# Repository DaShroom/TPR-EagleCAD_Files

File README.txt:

Ok, Tis licensed under CC-By Sa, which is at the bottom

This is all the electronics stuff for the robot, nuff said

You can also use this under the terms of the CERN license

CREATIVE COMMONS CORPORATION IS NOT A LAW FIRM AND DOES NOT PROVIDE LEGAL SERVICES. DISTRIBUTION OF THIS LICENSE DOES NOT CREATE AN ATTORNEY-CLIENT RELATIONSHIP. CREATIVE COMMONS PROVIDES THIS INFORMATION ON AN "AS-IS" BASIS. CREATIVE COMMONS MAKES NO WARRANTIES REGARDING THE INFORMATION PROVIDED, AND DISCLAIMS LIABILITY FOR DAMAGES RESULTING FROM ITS USE.
License

THE WORK (AS DEFINED BELOW) IS PROVIDED UNDER THE TERMS OF THIS CREATIVE COMMONS PUBLIC LICENSE ("CCPL" OR "LICENSE"). THE WORK IS PROTECTED BY COPYRIGHT AND/OR OTHER APPLICABLE LAW. ANY USE OF THE WORK OTHER THAN AS AUTHORIZED UNDER THIS LICENSE OR COPYRIGHT LAW IS PROHIBITED.

BY EXERCISING ANY RIGHTS TO THE WORK PROVIDED HERE, YOU ACCEPT AND AGREE TO BE BOUND BY THE TERMS OF THIS LICENSE. TO THE EXTENT THIS LICENSE MAY BE CONSIDERED TO BE A CONTRACT, THE LICENSOR GRANTS YOU THE RIGHTS CONTAINED HERE IN CONSIDERATION OF YOUR ACCEPTANCE OF SUCH TERMS AND CONDITIONS.

1. Definitions

"Adaptation" means a work based upon the Work, or upon the Work and other pre-existing works, such as a translation, adaptation, derivative work, arrangement of music or other alterations of a literary or artistic work, or phonogram or performance and includes cinematographic adaptations or any other form in which the Work may be recast, transformed, or adapted including in any form recognizably derived from the original, except that a work that constitutes a Collection will not be considered an Adaptation for the purpose of this License. For the avoidance of doubt, where the Work is a musical work, performance or phonogram, the synchronization of the Work in timed-relation with a moving image ("synching") will be considered an Adaptation for the purpose of this License.
"Collection" means a collection of literary or artistic works, such as encyclopedias and anthologies, or performances, phonograms or broadcasts, or other works or subject matter other than works listed in Section 1(f) below, which, by reason of the selection and arrangement of their contents, constitute intellectual creations, in which the Work is included in its entirety in unmodified form along with one or more other contributions, each constituting separate and independent works in themselves, which together are assembled into a collective whole. A work that constitutes a Collection will not be considered an Adaptation (as defined below) for the purposes of this License.
"Creative Commons Compatible License" means a license that is listed at http://creativecommons.org/compatiblelicenses that has been approved by Creative Commons as being essentially equivalent to this License, including, at a minimum, because that license: (i) contains terms that have the same purpose, meaning and effect as the License Elements of this License; and, (ii) explicitly permits the relicensing of adaptations of works made available under that license under this License or a Creative Commons jurisdiction license with the same License Elements as this License.
"Distribute" means to make available to the public the original and copies of the Work or Adaptation, as appropriate, through sale or other transfer of ownership.
"License Elements" means the following high-level license attributes as selected by Licensor and indicated in the title of this License: Attribution, ShareAlike.
"Licensor" means the individual, individuals, entity or entities that offer(s) the Work under the terms of this License.
"Original Author" means, in the case of a literary or artistic work, the individual, individuals, entity or entities who created the Work or if no individual or entity can be identified, the publisher; and in addition (i) in the case of a performance the actors, singers, musicians, dancers, and other persons who act, sing, deliver, declaim, play in, interpret or otherwise perform literary or artistic works or expressions of folklore; (ii) in the case of a phonogram the producer being the person or legal entity who first fixes the sounds of a performance or other sounds; and, (iii) in the case of broadcasts, the organization that transmits the broadcast.
"Work" means the literary and/or artistic work offered under the terms of this License including without limitation any production in the literary, scientific and artistic domain, whatever may be the mode or form of its expression including digital form, such as a book, pamphlet and other writing; a lecture, address, sermon or other work of the same nature; a dramatic or dramatico-musical work; a choreographic work or entertainment in dumb show; a musical composition with or without words; a cinematographic work to which are assimilated works expressed by a process analogous to cinematography; a work of drawing, painting, architecture, sculpture, engraving or lithography; a photographic work to which are assimilated works expressed by a process analogous to photography; a work of applied art; an illustration, map, plan, sketch or three-dimensional work relative to geography, topography, architecture or science; a performance; a broadcast; a phonogram; a compilation of data to the extent it is protected as a copyrightable work; or a work performed by a variety or circus performer to the extent it is not otherwise considered a literary or artistic work.
"You" means an individual or entity exercising rights under this License who has not previously violated the terms of this License with respect to the Work, or who has received express permission from the Licensor to exercise rights under this License despite a previous violation.
"Publicly Perform" means to perform public recitations of the Work and to communicate to the public those public recitations, by any means or process, including by wire or wireless means or public digital performances; to make available to the public Works in such a way that members of the public may access these Works from a place and at a place individually chosen by them; to perform the Work to the public by any means or process and the communication to the public of the performances of the Work, including by public digital performance; to broadcast and rebroadcast the Work by any means including signs, sounds or images.
"Reproduce" means to make copies of the Work by any means including without limitation by sound or visual recordings and the right of fixation and reproducing fixations of the Work, including storage of a protected performance or phonogram in digital form or other electronic medium.
2. Fair Dealing Rights. Nothing in this License is intended to reduce, limit, or restrict any uses free from copyright or rights arising from limitations or exceptions that are provided for in connection with the copyright protection under copyright law or other applicable laws.

3. License Grant. Subject to the terms and conditions of this License, Licensor hereby grants You a worldwide, royalty-free, non-exclusive, perpetual (for the duration of the applicable copyright) license to exercise the rights in the Work as stated below:

to Reproduce the Work, to incorporate the Work into one or more Collections, and to Reproduce the Work as incorporated in the Collections;
to create and Reproduce Adaptations provided that any such Adaptation, including any translation in any medium, takes reasonable steps to clearly label, demarcate or otherwise identify that changes were made to the original Work. For example, a translation could be marked "The original work was translated from English to Spanish," or a modification could indicate "The original work has been modified.";
to Distribute and Publicly Perform the Work including as incorporated in Collections; and,
to Distribute and Publicly Perform Adaptations.
For the avoidance of doubt:

Non-waivable Compulsory License Schemes. In those jurisdictions in which the right to collect royalties through any statutory or compulsory licensing scheme cannot be waived, the Licensor reserves the exclusive right to collect such royalties for any exercise by You of the rights granted under this License;
Waivable Compulsory License Schemes. In those jurisdictions in which the right to collect royalties through any statutory or compulsory licensing scheme can be waived, the Licensor waives the exclusive right to collect such royalties for any exercise by You of the rights granted under this License; and,
Voluntary License Schemes. The Licensor waives the right to collect royalties, whether individually or, in the event that the Licensor is a member of a collecting society that administers voluntary licensing schemes, via that society, from any exercise by You of the rights granted under this License.
The above rights may be exercised in all media and formats whether now known or hereafter devised. The above rights include the right to make such modifications as are technically necessary to exercise the rights in other media and formats. Subject to Section 8(f), all rights not expressly granted by Licensor are hereby reserved.

4. Restrictions. The license granted in Section 3 above is expressly made subject to and limited by the following restrictions:

You may Distribute or Publicly Perform the Work only under the terms of this License. You must include a copy of, or the Uniform Resource Identifier (URI) for, this License with every copy of the Work You Distribute or Publicly Perform. You may not offer or impose any terms on the Work that restrict the terms of this License or the ability of the recipient of the Work to exercise the rights granted to that recipient under the terms of the License. You may not sublicense the Work. You must keep intact all notices that refer to this License and to the disclaimer of warranties with every copy of the Work You Distribute or Publicly Perform. When You Distribute or Publicly Perform the Work, You may not impose any effective technological measures on the Work that restrict the ability of a recipient of the Work from You to exercise the rights granted to that recipient under the terms of the License. This Section 4(a) applies to the Work as incorporated in a Collection, but this does not require the Collection apart from the Work itself to be made subject to the terms of this License. If You create a Collection, upon notice from any Licensor You must, to the extent practicable, remove from the Collection any credit as required by Section 4(c), as requested. If You create an Adaptation, upon notice from any Licensor You must, to the extent practicable, remove from the Adaptation any credit as required by Section 4(c), as requested.
You may Distribute or Publicly Perform an Adaptation only under the terms of: (i) this License; (ii) a later version of this License with the same License Elements as this License; (iii) a Creative Commons jurisdiction license (either this or a later license version) that contains the same License Elements as this License (e.g., Attribution-ShareAlike 3.0 US)); (iv) a Creative Commons Compatible License. If you license the Adaptation under one of the licenses mentioned in (iv), you must comply with the terms of that license. If you license the Adaptation under the terms of any of the licenses mentioned in (i), (ii) or (iii) (the "Applicable License"), you must comply with the terms of the Applicable License generally and the following provisions: (I) You must include a copy of, or the URI for, the Applicable License with every copy of each Adaptation You Distribute or Publicly Perform; (II) You may not offer or impose any terms on the Adaptation that restrict the terms of the Applicable License or the ability of the recipient of the Adaptation to exercise the rights granted to that recipient under the terms of the Applicable License; (III) You must keep intact all notices that refer to the Applicable License and to the disclaimer of warranties with every copy of the Work as included in the Adaptation You Distribute or Publicly Perform; (IV) when You Distribute or Publicly Perform the Adaptation, You may not impose any effective technological measures on the Adaptation that restrict the ability of a recipient of the Adaptation from You to exercise the rights granted to that recipient under the terms of the Applicable License. This Section 4(b) applies to the Adaptation as incorporated in a Collection, but this does not require the Collection apart from the Adaptation itself to be made subject to the terms of the Applicable License.
If You Distribute, or Publicly Perform the Work or any Adaptations or Collections, You must, unless a request has been made pursuant to Section 4(a), keep intact all copyright notices for the Work and provide, reasonable to the medium or means You are utilizing: (i) the name of the Original Author (or pseudonym, if applicable) if supplied, and/or if the Original Author and/or Licensor designate another party or parties (e.g., a sponsor institute, publishing entity, journal) for attribution ("Attribution Parties") in Licensor's copyright notice, terms of service or by other reasonable means, the name of such party or parties; (ii) the title of the Work if supplied; (iii) to the extent reasonably practicable, the URI, if any, that Licensor specifies to be associated with the Work, unless such URI does not refer to the copyright notice or licensing information for the Work; and (iv) , consistent with Ssection 3(b), in the case of an Adaptation, a credit identifying the use of the Work in the Adaptation (e.g., "French translation of the Work by Original Author," or "Screenplay based on original Work by Original Author"). The credit required by this Section 4(c) may be implemented in any reasonable manner; provided, however, that in the case of a Adaptation or Collection, at a minimum such credit will appear, if a credit for all contributing authors of the Adaptation or Collection appears, then as part of these credits and in a manner at least as prominent as the credits for the other contributing authors. For the avoidance of doubt, You may only use the credit required by this Section for the purpose of attribution in the manner set out above and, by exercising Your rights under this License, You may not implicitly or explicitly assert or imply any connection with, sponsorship or endorsement by the Original Author, Licensor and/or Attribution Parties, as appropriate, of You or Your use of the Work, without the separate, express prior written permission of the Original Author, Licensor and/or Attribution Parties.
Except as otherwise agreed in writing by the Licensor or as may be otherwise permitted by applicable law, if You Reproduce, Distribute or Publicly Perform the Work either by itself or as part of any Adaptations or Collections, You must not distort, mutilate, modify or take other derogatory action in relation to the Work which would be prejudicial to the Original Author's honor or reputation. Licensor agrees that in those jurisdictions (e.g. Japan), in which any exercise of the right granted in Section 3(b) of this License (the right to make Adaptations) would be deemed to be a distortion, mutilation, modification or other derogatory action prejudicial to the Original Author's honor and reputation, the Licensor will waive or not assert, as appropriate, this Section, to the fullest extent permitted by the applicable national law, to enable You to reasonably exercise Your right under Section 3(b) of this License (right to make Adaptations) but not otherwise.
5. Representations, Warranties and Disclaimer

UNLESS OTHERWISE MUTUALLY AGREED TO BY THE PARTIES IN WRITING, LICENSOR OFFERS THE WORK AS-IS AND MAKES NO REPRESENTATIONS OR WARRANTIES OF ANY KIND CONCERNING THE WORK, EXPRESS, IMPLIED, STATUTORY OR OTHERWISE, INCLUDING, WITHOUT LIMITATION, WARRANTIES OF TITLE, MERCHANTIBILITY, FITNESS FOR A PARTICULAR PURPOSE, NONINFRINGEMENT, OR THE ABSENCE OF LATENT OR OTHER DEFECTS, ACCURACY, OR THE PRESENCE OF ABSENCE OF ERRORS, WHETHER OR NOT DISCOVERABLE. SOME JURISDICTIONS DO NOT ALLOW THE EXCLUSION OF IMPLIED WARRANTIES, SO SUCH EXCLUSION MAY NOT APPLY TO YOU.

6. Limitation on Liability. EXCEPT TO THE EXTENT REQUIRED BY APPLICABLE LAW, IN NO EVENT WILL LICENSOR BE LIABLE TO YOU ON ANY LEGAL THEORY FOR ANY SPECIAL, INCIDENTAL, CONSEQUENTIAL, PUNITIVE OR EXEMPLARY DAMAGES ARISING OUT OF THIS LICENSE OR THE USE OF THE WORK, EVEN IF LICENSOR HAS BEEN ADVISED OF THE POSSIBILITY OF SUCH DAMAGES.

7. Termination

This License and the rights granted hereunder will terminate automatically upon any breach by You of the terms of this License. Individuals or entities who have received Adaptations or Collections from You under this License, however, will not have their licenses terminated provided such individuals or entities remain in full compliance with those licenses. Sections 1, 2, 5, 6, 7, and 8 will survive any termination of this License.
Subject to the above terms and conditions, the license granted here is perpetual (for the duration of the applicable copyright in the Work). Notwithstanding the above, Licensor reserves the right to release the Work under different license terms or to stop distributing the Work at any time; provided, however that any such election will not serve to withdraw this License (or any other license that has been, or is required to be, granted under the terms of this License), and this License will continue in full force and effect unless terminated as stated above.
8. Miscellaneous

Each time You Distribute or Publicly Perform the Work or a Collection, the Licensor offers to the recipient a license to the Work on the same terms and conditions as the license granted to You under this License.
Each time You Distribute or Publicly Perform an Adaptation, Licensor offers to the recipient a license to the original Work on the same terms and conditions as the license granted to You under this License.
If any provision of this License is invalid or unenforceable under applicable law, it shall not affect the validity or enforceability of the remainder of the terms of this License, and without further action by the parties to this agreement, such provision shall be reformed to the minimum extent necessary to make such provision valid and enforceable.
No term or provision of this License shall be deemed waived and no breach consented to unless such waiver or consent shall be in writing and signed by the party to be charged with such waiver or consent.
This License constitutes the entire agreement between the parties with respect to the Work licensed here. There are no understandings, agreements or representations with respect to the Work not specified here. Licensor shall not be bound by any additional provisions that may appear in any communication from You. This License may not be modified without the mutual written agreement of the Licensor and You.
The rights granted under, and the subject matter referenced, in this License were drafted utilizing the terminology of the Berne Convention for the Protection of Literary and Artistic Works (as amended on September 28, 1979), the Rome Convention of 1961, the WIPO Copyright Treaty of 1996, the WIPO Performances and Phonograms Treaty of 1996 and the Universal Copyright Convention (as revised on July 24, 1971). These rights and subject matter take effect in the relevant jurisdiction in which the License terms are sought to be enforced according to the corresponding provisions of the implementation of those treaty provisions in the applicable national law. If the standard suite of rights granted under applicable copyright law includes additional rights not granted under this License, such additional rights are deemed to be included in the License; this License is not intended to restrict the license of any rights under applicable law.
Creative Commons Notice

Creative Commons is not a party to this License, and makes no warranty whatsoever in connection with the Work. Creative Commons will not be liable to You or any party on any legal theory for any damages whatsoever, including without limitation any general, special, incidental or consequential damages arising in connection to this license. Notwithstanding the foregoing two (2) sentences, if Creative Commons has expressly identified itself as the Licensor hereunder, it shall have all rights and obligations of Licensor.

Except for the limited purpose of indicating to the public that the Work is licensed under the CCPL, Creative Commons does not authorize the use by either party of the trademark "Creative Commons" or any related trademark or logo of Creative Commons without the prior written consent of Creative Commons. Any permitted use will be in compliance with Creative Commons' then-current trademark usage guidelines, as may be published on its website or otherwise made available upon request from time to time. For the avoidance of doubt, this trademark restriction does not form part of the License.

Creative Commons may be contacted at http://creativecommons.org/.

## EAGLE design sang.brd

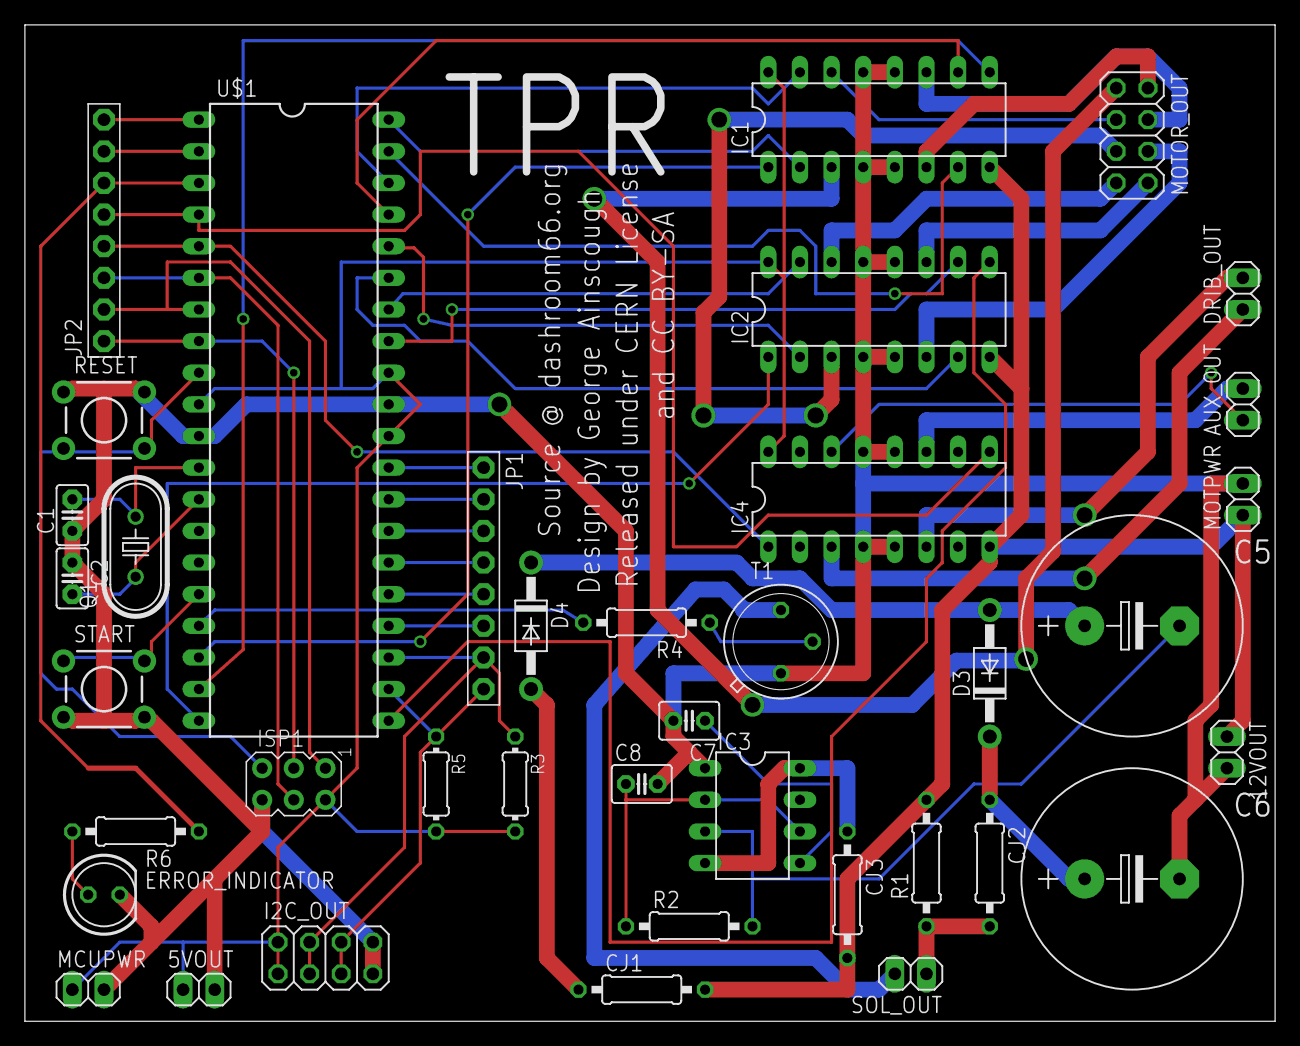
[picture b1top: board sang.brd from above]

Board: 2 copper layers, 100.4 x 80.0 mm, 39 parts (0 on the bottom side), 59 nets.

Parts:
5VOUT, 12VOUT: 1X02
AUX_OUT: 1X02
C1, C2: 22pF; C2.5-2
C5, C6: E7,5-18
C7: 100nF; C025-030X050
C8: 1nF; C025-030X050
CJ1, CJ2, CJ3: 0207/10
D3, D4: 1N4004; DO41-10
DRIB_OUT: 1X02
ERROR_INDICATOR: LED5MM
I2C_OUT: 2X04
IC1, IC2, IC4: L293D; DIL16
IC3: NE555; DIL-08
ISP1: AVRISP-6; AVRISP
JP1, JP2: 1X08-BIG
MCUPWR: 1X02
MOTOR_OUT: 2X04
MOTPWR: 1X02
Q1: 16MHz; HC49U70
R1, R4: 10K; 0207/10
R2: 33K; 0207/10
R3, R5: 0204/7
R6: 220; 0207/10
RESET: TACTILE-PTH
SOL_OUT: 1X02
START: TACTILE-PTH
T1: TO39
U$1: ATMEGA644*; ATMEGA644

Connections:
+5V: 5VOUT.1, I2C_OUT.1, I2C_OUT.2, IC1.16, IC2.16, IC4.16, ISP1.2, MCUPWR.1, R3.2, R5.2, U$1.10, U$1.30, U$1.32
+12V: 12VOUT.1, CJ1.2, CJ3.2, IC1.8, IC2.8, IC4.8, MOTPWR.1, R1.2
+24V: CJ2.2, R1.1, SOL_OUT.1
ERROR_LED: JP2.6, R6.1, U$1.3
GND: 5VOUT.2, 12VOUT.2, C1.1, C2.1, C6.-, C7.2, C8.2, ERROR_INDICATOR.K, I2C_OUT.7, I2C_OUT.8, IC1.4, IC1.5, IC1.12, IC1.13, IC2.4, IC2.5, IC2.12, IC2.13, IC3.1, IC4.4, IC4.5, IC4.12, IC4.13, ISP1.6, MCUPWR.2, MOTPWR.2, RESET.1, RESET.2, START.3, START.4, T1.1, U$1.11, U$1.31
GO: START.1, START.2, U$1.16
M1+: IC1.3, MOTOR_OUT.1
M1-: IC1.6, MOTOR_OUT.2
M1F: IC1.2, U$1.40
M1PWM: IC1.1, U$1.18
M1R: IC1.7, U$1.39
M2+: IC1.14, MOTOR_OUT.3
M2-: IC1.11, MOTOR_OUT.4
M2F: IC1.15, U$1.38
M2PWM: IC1.9, U$1.19
M2R: IC1.10, U$1.37
M3+: IC2.3, MOTOR_OUT.5
M3-: IC2.6, MOTOR_OUT.6
M3F: IC2.2, U$1.36
M3PWM: IC2.1, U$1.20
M3R: IC2.7, U$1.35
M4+: IC2.14, MOTOR_OUT.7
M4-: IC2.11, MOTOR_OUT.8
M4F: IC2.15, U$1.34
M4PWM: IC2.9, U$1.21
M4R: IC2.10, U$1.33
M5+: DRIB_OUT.1, IC4.3
M5-: DRIB_OUT.2, IC4.6
M5PWM: IC4.1, JP2.4, U$1.5
M6+: AUX_OUT.1, IC4.14
M6-: AUX_OUT.2, IC4.11
M6PWM: IC4.9, JP2.5, U$1.4
MISO: ISP1.1, JP2.2, U$1.7
MOSI: ISP1.4, JP2.3, U$1.6
unnamed: C1.2, Q1.2, U$1.12
unnamed: C2.2, Q1.1, U$1.13
unnamed: C8.1, IC3.2, IC3.6, R2.1
unnamed: R4.1, T1.2
unnamed: C5.-, IC3.3, R2.2
unnamed: C5.+, D3.A, D4.C
unnamed: SOL_OUT.2, T1.3
unnamed: JP1.6, U$1.24
unnamed: C7.1, IC3.5
unnamed: JP1.5, U$1.25
unnamed: JP1.4, U$1.26
unnamed: JP1.3, U$1.27
unnamed: JP1.2, U$1.28
unnamed: JP1.1, U$1.29
unnamed: JP2.8, U$1.1
unnamed: JP2.7, U$1.2
unnamed: C6.+, CJ2.1, D3.C
unnamed: CJ1.1, D4.A
unnamed: CJ3.1, IC3.4, IC3.8
unnamed: ERROR_INDICATOR.A, R6.2
RST: ISP1.5, RESET.3, RESET.4, U$1.9
SCK: ISP1.3, JP2.1, U$1.8
SCL: I2C_OUT.5, I2C_OUT.6, JP1.8, R5.1, U$1.22
SDA: I2C_OUT.3, I2C_OUT.4, JP1.7, R3.1, U$1.23
SOLSIG: R4.2, U$1.17

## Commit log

2012-08-19 Initial Upload
    Untested .etc
2012-08-20 Very little
    Don't think I changed nout, but git says I have...
2012-09-01 Pins BrokenOut - Pullups Changed
    Internal Pull ups to be used, aded I2C pullups
    Broke ut unused pin
2012-10-07 Dribbler Driver Added...
    along with debug LED, and a new layout. Kind of a big commit :-D
2012-12-13 Alpha 1
    Branding and layout changed

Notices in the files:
README.txt:
Individuals or entities who have received Adaptations or Collections from You under this License, however, will not have their licenses terminated provided such individuals or entities remain in full compliance with those licenses.
Notwithstanding the above, Licensor reserves the right to release the Work under different license terms or to stop distributing the Work at any time; provided, however that any such election will not serve to withdraw this License (or any other license that has been, or is required to be, granted
Creative Commons Notice
sang.brd:
and CC BY-SA
